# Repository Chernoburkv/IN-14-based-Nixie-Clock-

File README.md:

# IN-14-based-Nixie-Clock-
Nixie clock with date and calendar on 6 soviet nixie tubes with static indication and voltage doubler for nixies. 
Based on ds3231 and ATmega 8. Powers from 36-42VAC (for example a small transformer).
ECAD files for main & display board, Code::Blocks project, hex and fuse pic included.

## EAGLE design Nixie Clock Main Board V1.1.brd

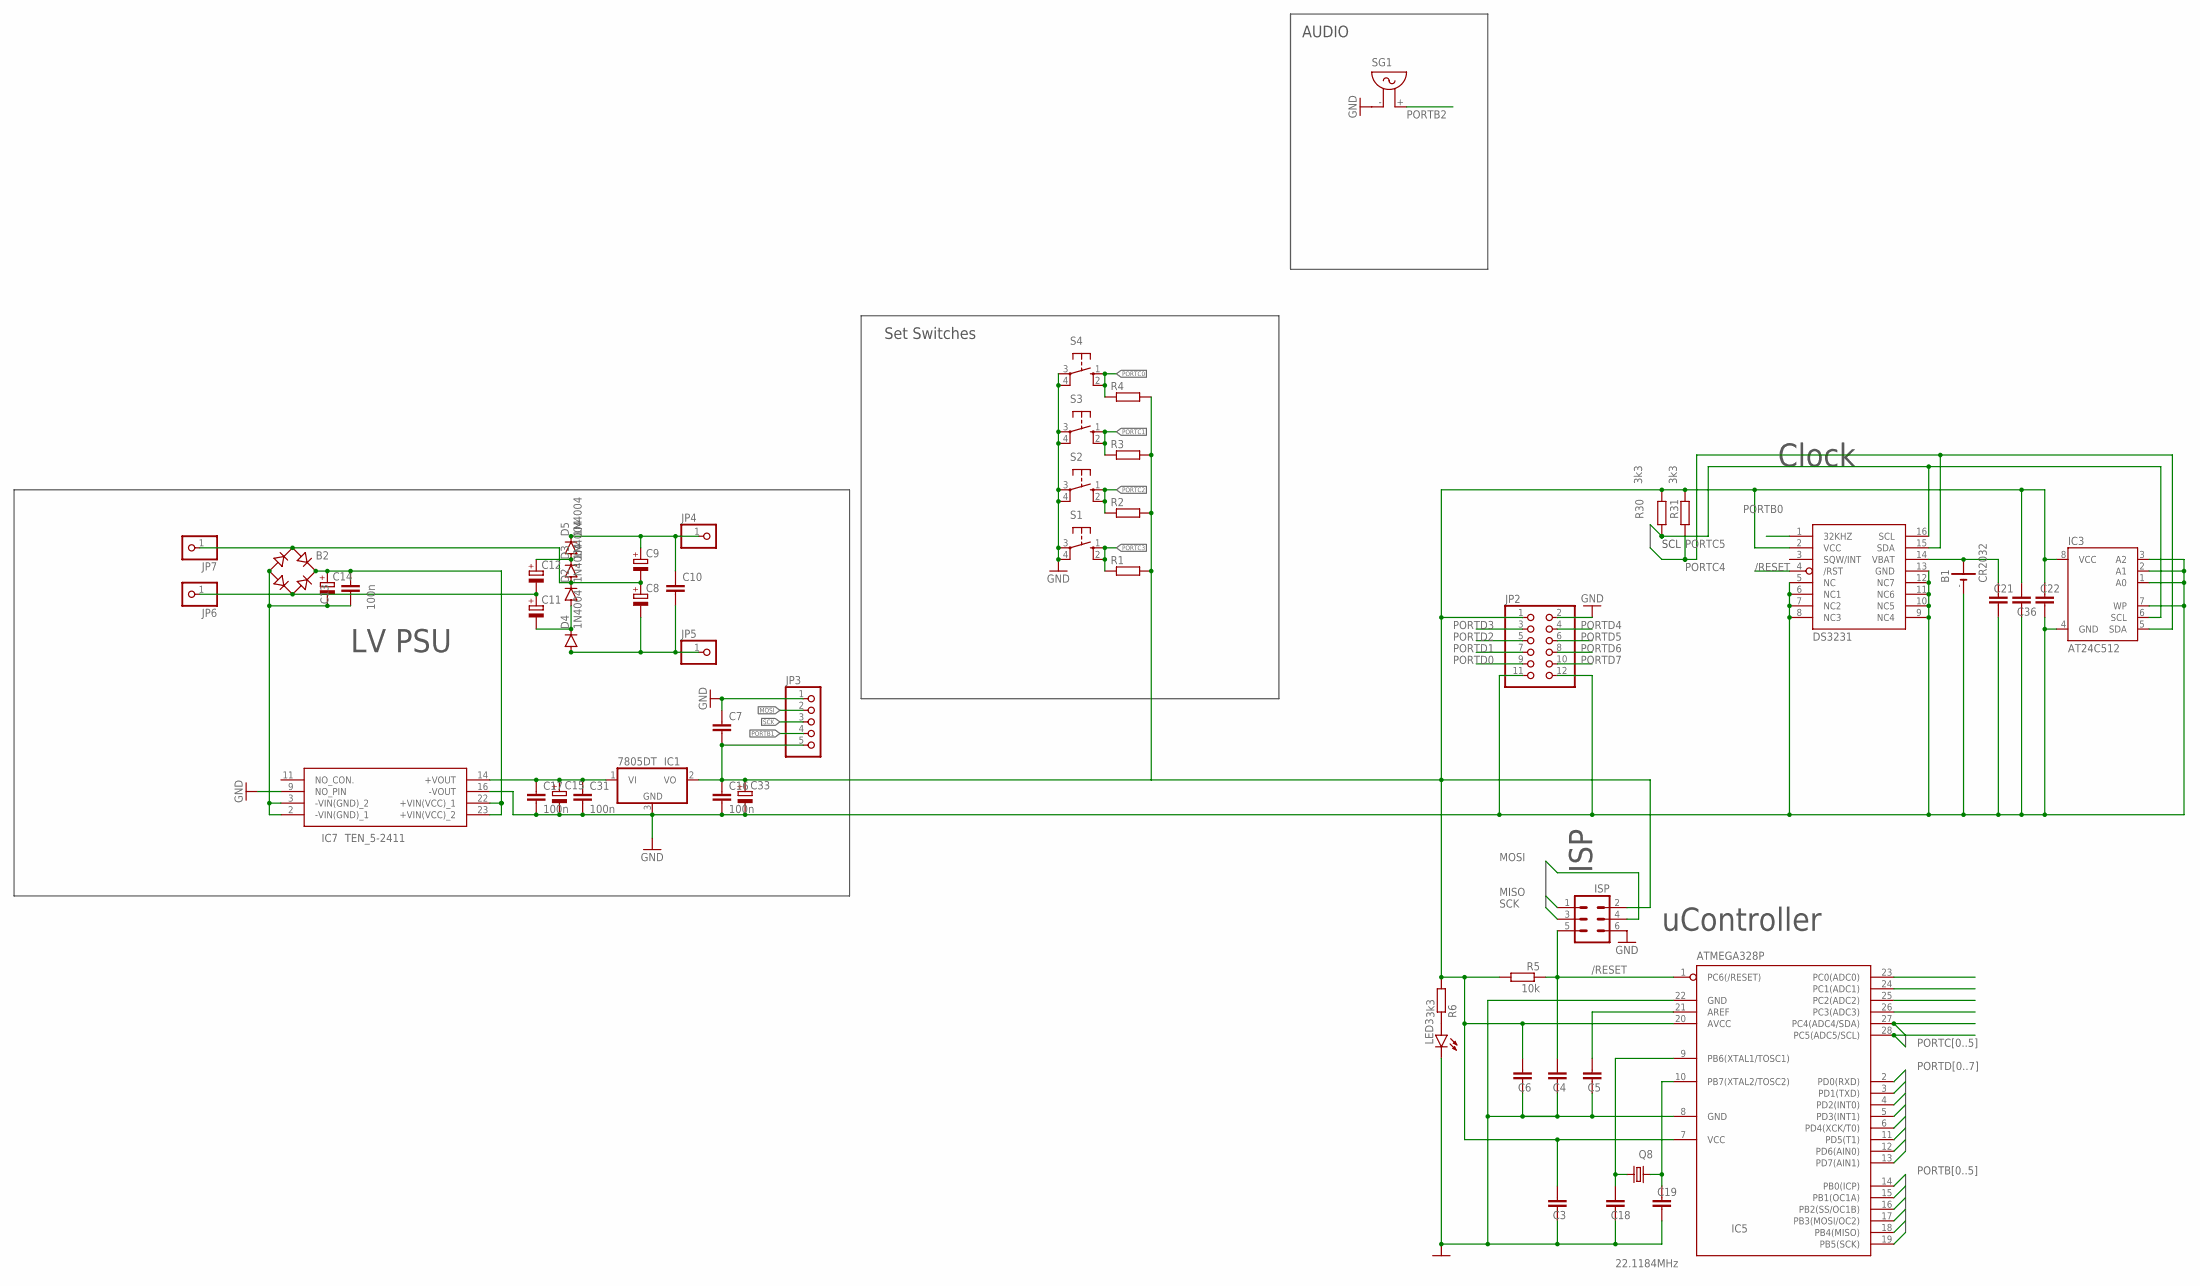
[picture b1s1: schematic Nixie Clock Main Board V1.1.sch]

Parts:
B1: CR2032
B2: B-DIL
C3, C5, C6, C21, C22, C36: C-EUC1206; C1206
C4, C7, C18, C19: C-EUC0805; C0805
C8, C9, C11, C12, C14: CPOL-EUTT5D11; TT5D11
C10: C-EU150-054X183; C150-054X183
C13: 100n; C050-025X075
C15, C33: CPOL-EUE3.5-8; E3,5-8
C16, C17, C31: 100n; C1206
D2, D3, D4, D5: 1N4004; DO41-10
IC1: 7805DT; TO252
IC3: AT24C512; DIL08
IC5: ATMEGA328P; DIL28-3
IC7: TEN_5-2411; TEN5SERIES
J: ISP; MA03-2
JP2: PINHD-2X6; 2X06
JP3: PINHD-1X5; 1X05
JP4, JP5, JP6, JP7: PINHD-1X1; 1X01
LED3: LED5MM
Q8: 22.1184MHz; HC49U-V
R1, R2, R3, R4: R-EU_R0805; R0805
R5: 10k; R0805
R6, R30, R31: 3k3; R0805
S1, S2, S3, S4: 10-XX; B3F-10XX
SG1: F/QMX
U2: DS3231; SO16W

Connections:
+5V: C3.1, C6.1, C7.2, C16.1, C22.1, C33.+, C36.1, IC1.2 (VO), IC3.8 (VCC), IC5.7 (VCC), IC5.20 (AVCC), J.2, JP2.1, JP3.5, R1.2, R2.2, R3.2, R4.2, R5.2, R6.2, R30.2, R31.2, U2.2 (VCC)
/RESET: C4.1, IC5.1 (PC6(/RESET)), J.5, R5.1, U2.4 (/RST)
GND: B1.-, C3.2, C4.2, C5.2, C6.2, C7.1, C15.-, C16.2, C17.2, C18.2, C19.2, C21.2, C22.2, C31.2, C33.-, C36.2, IC1.3 (GND), IC3.1 (A0), IC3.2 (A1), IC3.3 (A2), IC3.4 (GND), IC3.7 (WP), IC5.8 (GND), IC5.22 (GND), IC7.9 (NO_PIN), IC7.16 (-VOUT), J.6, JP2.2, JP2.11, JP2.12, JP3.1, LED3.K (C), S1.3, S1.4 (P1), S2.3, S2.4 (P1), S3.3, S3.4 (P1), S4.3, S4.4 (P1), SG1.- (1), U2.5 (NC), U2.6 (NC1), U2.7 (NC2), U2.8 (NC3), U2.9 (NC4), U2.10 (NC5), U2.11 (NC6), U2.12 (NC7), U2.13 (GND)
MISO: IC5.18 (PB4(MISO)), J.1
MOSI: IC5.17 (PB3(MOSI/OC2)), J.4, JP3.2
unnamed: C12.+, D3.C, D5.A
unnamed: B2.AC1, C8.+, C9.-, D2.C, D3.A, JP7.1
unnamed: C11.-, D2.A, D4.C
unnamed: B2.AC2, C11.+, C12.-, JP6.1
unnamed: B2.+, C13.2, C14.+, IC7.22 (+VIN(VCC)_1), IC7.23 (+VIN(VCC)_2)
unnamed: C8.-, C10.2, D4.A, JP5.1
unnamed: C9.+, C10.1, D5.C, JP4.1
unnamed: LED3.A, R6.1
unnamed: B2.-, C13.1, C14.-, IC7.2 (-VIN(GND)_1), IC7.3 (-VIN(GND)_2)
unnamed: C18.1, IC5.9 (PB6(XTAL1/TOSC1)), Q8.1
unnamed: C19.1, IC5.10 (PB7(XTAL2/TOSC2)), Q8.2
unnamed: B1.+, C21.1, U2.14 (VBAT)
unnamed: C5.1, IC5.21 (AREF)
unnamed: C15.+, C17.1, C31.1, IC1.1 (VI), IC7.14 (+VOUT)
PORTB0: IC5.14 (PB0(ICP)), U2.1 (32KHZ)
PORTB1: IC5.15 (PB1(OC1A)), JP3.4
PORTB2: IC5.16 (PB2(SS/OC1B)), SG1.+ (2)
PORTC0: IC5.23 (PC0(ADC0)), R4.1, S4.1 (S), S4.2 (S1)
PORTC1: IC5.24 (PC1(ADC1)), R3.1, S3.1 (S), S3.2 (S1)
PORTC2: IC5.25 (PC2(ADC2)), R2.1, S2.1 (S), S2.2 (S1)
PORTC3: IC5.26 (PC3(ADC3)), R1.1, S1.1 (S), S1.2 (S1)
PORTC4: IC3.5 (SDA), IC5.27 (PC4(ADC4/SDA)), R31.1, U2.15 (SDA)
PORTC5: IC3.6 (SCL), IC5.28 (PC5(ADC5/SCL)), R30.1, U2.16 (SCL)
PORTD0: IC5.2 (PD0(RXD)), JP2.9
PORTD1: IC5.3 (PD1(TXD)), JP2.7
PORTD2: IC5.4 (PD2(INT0)), JP2.5
PORTD3: IC5.5 (PD3(INT1)), JP2.3
PORTD4: IC5.6 (PD4(XCK/T0)), JP2.4
PORTD5: IC5.11 (PD5(T1)), JP2.6
PORTD6: IC5.12 (PD6(AIN0)), JP2.8
PORTD7: IC5.13 (PD7(AIN1)), JP2.10
SCK: IC5.19 (PB5(SCK)), J.3, JP3.3

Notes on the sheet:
Set Switches
AUDIO
LV PSU
Clock
uController
SCL
ISP

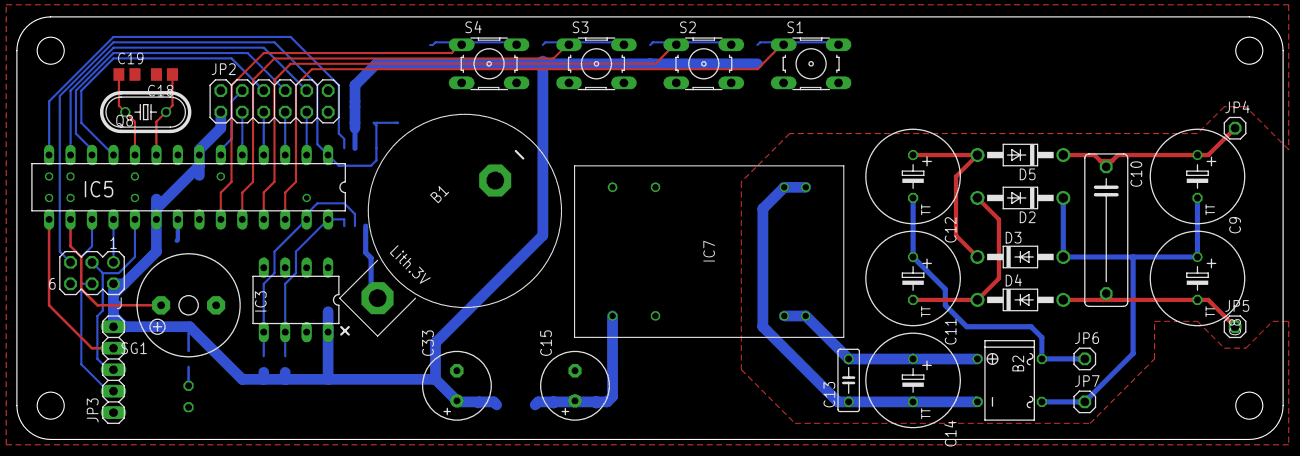
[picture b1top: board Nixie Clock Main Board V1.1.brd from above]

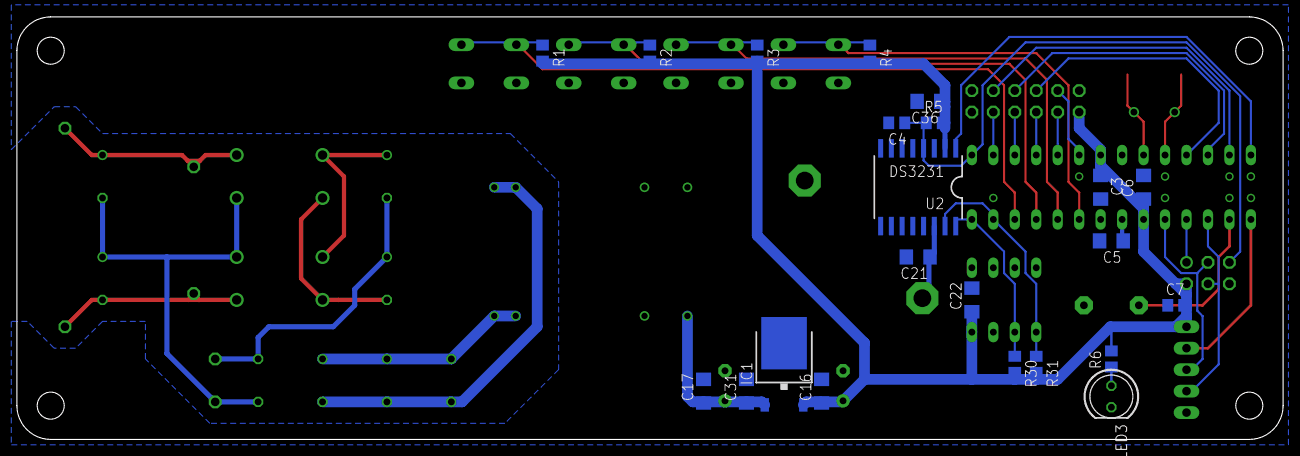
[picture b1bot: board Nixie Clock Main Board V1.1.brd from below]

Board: 2 copper layers, 149.8 x 50.0 mm, 56 parts (22 on the bottom side), 37 nets.

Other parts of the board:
U$3: 50X150

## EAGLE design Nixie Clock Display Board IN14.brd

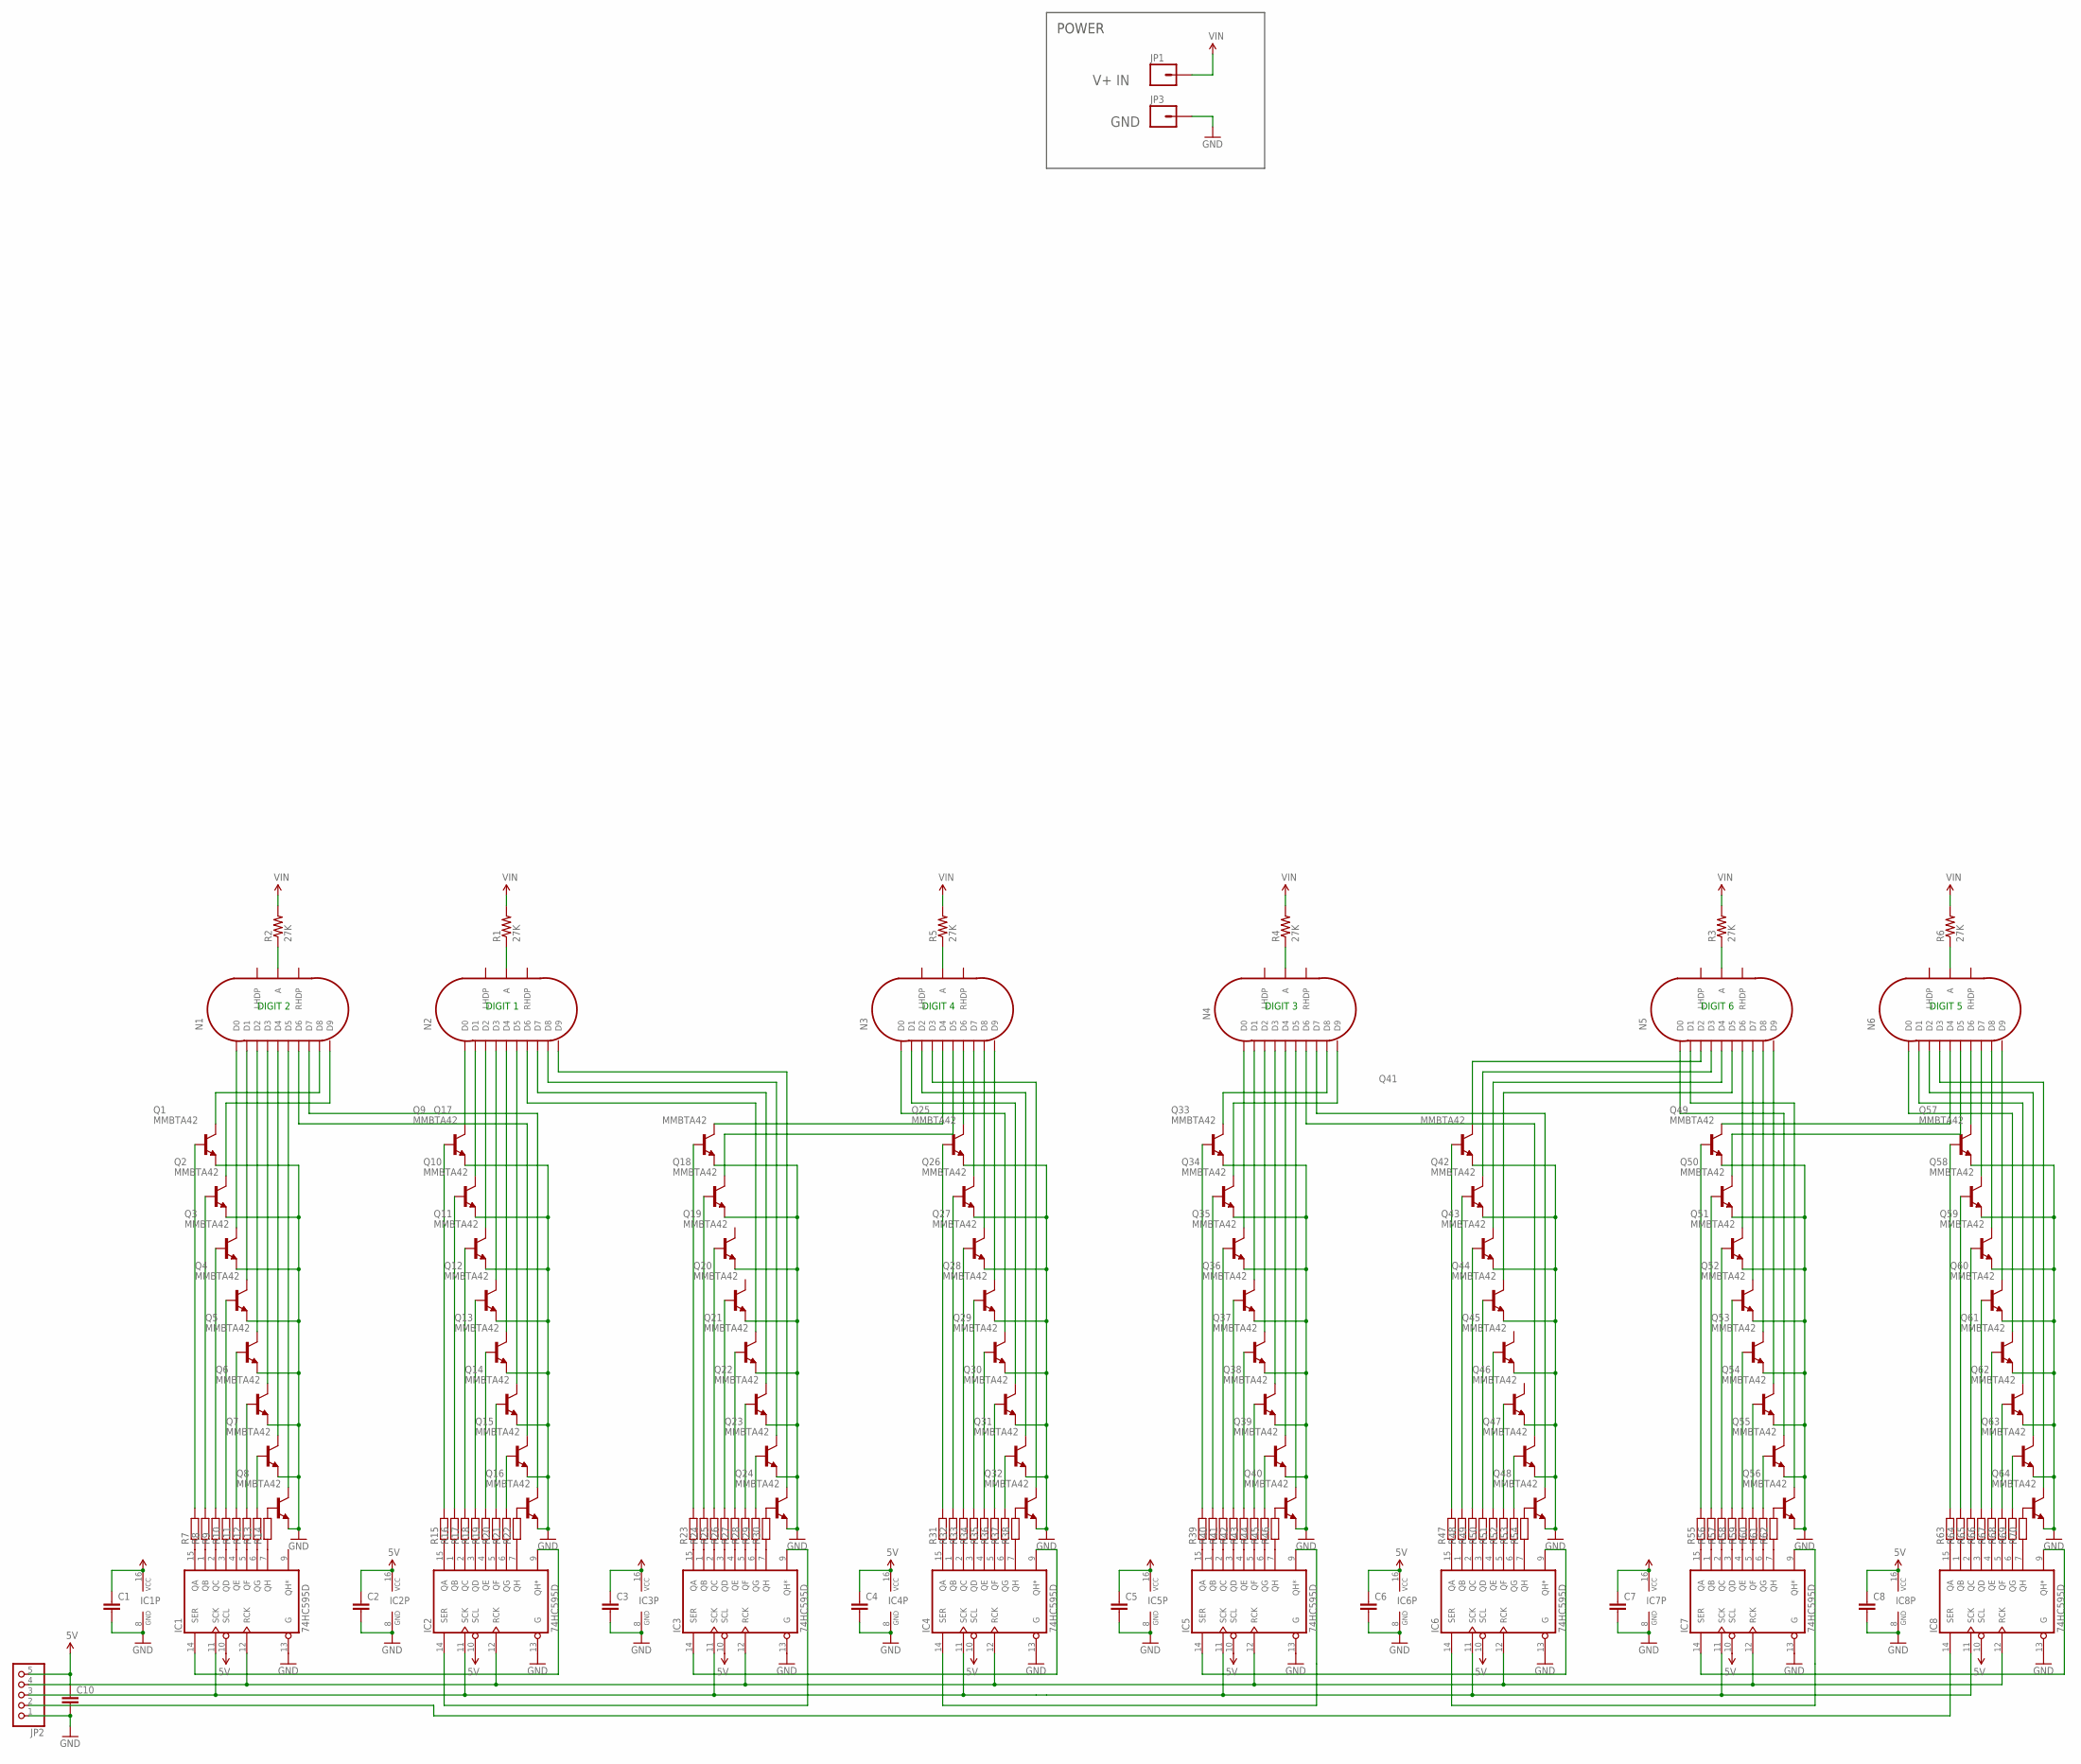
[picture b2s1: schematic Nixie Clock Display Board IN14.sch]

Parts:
C1, C2, C3, C4, C5, C6, C7, C8, C10: C-EUC0805; C0805
IC1, IC2, IC3, IC4, IC5, IC6, IC7, IC8: 74HC595D; SO16
JP1, JP3: M01PTH; 1X01
JP2: PINHD-1X5; 1X05
N1, N2, N3, N4, N5, N6: IN-14
Q1, Q2, Q3, Q4, Q5, Q6, Q7, Q8, Q9, Q10, Q11, Q12, Q13, Q14, Q15, Q16, Q17, Q18, Q19, Q20, Q21, Q22, Q23, Q24, Q25, Q26, Q27, Q28, Q29, Q30, Q31, Q32, Q33, Q34, Q35, Q36, Q37, Q38, Q39, Q40, Q41, Q42, Q43, Q44, Q45, Q46, Q47, Q48, Q49, Q50, Q51, Q52, Q53, Q54, Q55, Q56, Q57, Q58, Q59, Q60, Q61, Q62, Q63, Q64: MMBTA42; SOT23
R1, R2, R3, R4, R5, R6: 27K; AXIAL-0.5
R7, R8, R9, R10, R11, R12, R13, R14, R15, R16, R17, R18, R19, R20, R21, R22, R23, R24, R25, R26, R27, R28, R29, R30, R31, R32, R33, R34, R35, R36, R37, R38, R39, R40, R41, R42, R43, R44, R45, R46, R47, R48, R49, R50, R51, R52, R53, R54, R55, R56, R57, R58, R59, R60, R61, R62, R63, R64, R65, R66, R67, R68, R69, R70: R-EU_R0805; R0805

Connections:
5V: C1.1, C2.1, C3.1, C4.1, C5.1, C6.1, C7.1, C8.1, C10.1, IC1.10 (SCL), IC1.16 (VCC), IC2.10 (SCL), IC2.16 (VCC), IC3.10 (SCL), IC3.16 (VCC), IC4.10 (SCL), IC4.16 (VCC), IC5.10 (SCL), IC5.16 (VCC), IC6.10 (SCL), IC6.16 (VCC), IC7.10 (SCL), IC7.16 (VCC), IC8.10 (SCL), IC8.16 (VCC), JP2.5
GND: C1.2, C2.2, C3.2, C4.2, C5.2, C6.2, C7.2, C8.2, C10.2, IC1.8 (GND), IC1.13 (G), IC2.8 (GND), IC2.13 (G), IC3.8 (GND), IC3.13 (G), IC4.8 (GND), IC4.13 (G), IC5.8 (GND), IC5.13 (G), IC6.8 (GND), IC6.13 (G), IC7.8 (GND), IC7.13 (G), IC8.8 (GND), IC8.13 (G), JP2.1, JP3.1, Q1.2 (E), Q2.2 (E), Q3.2 (E), Q4.2 (E), Q5.2 (E), Q6.2 (E), Q7.2 (E), Q8.2 (E), Q9.2 (E), Q10.2 (E), Q11.2 (E), Q12.2 (E), Q13.2 (E), Q14.2 (E), Q15.2 (E), Q16.2 (E), Q17.2 (E), Q18.2 (E), Q19.2 (E), Q20.2 (E), Q21.2 (E), Q22.2 (E), Q23.2 (E), Q24.2 (E), Q25.2 (E), Q26.2 (E), Q27.2 (E), Q28.2 (E), Q29.2 (E), Q30.2 (E), Q31.2 (E), Q32.2 (E), Q33.2 (E), Q34.2 (E), Q35.2 (E), Q36.2 (E), Q37.2 (E), Q38.2 (E), Q39.2 (E), Q40.2 (E), Q41.2 (E), Q42.2 (E), Q43.2 (E), Q44.2 (E), Q45.2 (E), Q46.2 (E), Q47.2 (E), Q48.2 (E), Q49.2 (E), Q50.2 (E), Q51.2 (E), Q52.2 (E), Q53.2 (E), Q54.2 (E), Q55.2 (E), Q56.2 (E), Q57.2 (E), Q58.2 (E), Q59.2 (E), Q60.2 (E), Q61.2 (E), Q62.2 (E), Q63.2 (E), Q64.2 (E)
IN1: IC8.14 (SER), JP2.2
IN2: IC1.12 (RCK), IC2.12 (RCK), IC3.12 (RCK), IC4.12 (RCK), IC5.12 (RCK), IC6.12 (RCK), IC7.12 (RCK), IC8.12 (RCK), JP2.4
IN5: IC1.11 (SCK), IC2.11 (SCK), IC3.11 (SCK), IC4.11 (SCK), IC5.11 (SCK), IC6.11 (SCK), IC7.11 (SCK), IC8.11 (SCK), JP2.3
IN7: IC2.14 (SER), IC3.9 (QH*)
IN8: IC4.14 (SER), IC5.9 (QH*)
IN12: IC5.14 (SER), IC6.9 (QH*)
IN13: IC6.14 (SER), IC7.9 (QH*)
unnamed: Q1.1 (B), R7.2
unnamed: IC1.15 (QA), R7.1
unnamed: IC1.1 (QB), R8.1
unnamed: IC1.2 (QC), R9.1
unnamed: IC1.3 (QD), R10.1
unnamed: IC1.4 (QE), R11.1
unnamed: IC1.5 (QF), R12.1
unnamed: IC1.6 (QG), R13.1
unnamed: IC1.7 (QH), R14.1
unnamed: Q8.1 (B), R14.2
unnamed: Q7.1 (B), R13.2
unnamed: Q6.1 (B), R12.2
unnamed: Q5.1 (B), R11.2
unnamed: Q4.1 (B), R10.2
unnamed: Q3.1 (B), R9.2
unnamed: Q2.1 (B), R8.2
unnamed: Q9.1 (B), R15.2
unnamed: Q16.1 (B), R22.2
unnamed: Q15.1 (B), R21.2
unnamed: Q14.1 (B), R20.2
unnamed: Q13.1 (B), R19.2
unnamed: Q12.1 (B), R18.2
unnamed: Q11.1 (B), R17.2
unnamed: Q10.1 (B), R16.2
unnamed: N6.D0, Q61.3 (C)
unnamed: IC1.14 (SER), IC2.9 (QH*)
unnamed: N5.A, R3.P$1 (1)
unnamed: IC2.15 (QA), R15.1
unnamed: IC2.1 (QB), R16.1
unnamed: IC2.2 (QC), R17.1
unnamed: IC2.3 (QD), R18.1
unnamed: IC2.4 (QE), R19.1
unnamed: IC2.5 (QF), R20.1
unnamed: IC2.6 (QG), R21.1
unnamed: IC2.7 (QH), R22.1
unnamed: Q17.1 (B), R23.2
unnamed: Q24.1 (B), R30.2
unnamed: N6.A, R6.P$1 (1)
unnamed: Q23.1 (B), R29.2
unnamed: Q22.1 (B), R28.2
unnamed: Q21.1 (B), R27.2
unnamed: Q20.1 (B), R26.2
unnamed: Q19.1 (B), R25.2
unnamed: Q18.1 (B), R24.2
unnamed: IC3.15 (QA), R23.1
unnamed: IC3.1 (QB), R24.1
unnamed: IC3.2 (QC), R25.1
unnamed: IC3.3 (QD), R26.1
unnamed: IC3.4 (QE), R27.1
unnamed: IC3.5 (QF), R28.1
unnamed: IC3.6 (QG), R29.1
unnamed: IC3.7 (QH), R30.1
unnamed: N4.A, R4.P$1 (1)
unnamed: N3.A, R5.P$1 (1)
unnamed: IC3.14 (SER), IC4.9 (QH*)
unnamed: N6.D1, Q62.3 (C)
unnamed: IC7.14 (SER), IC8.9 (QH*)
unnamed: N6.D2, Q63.3 (C)
unnamed: N6.D3, Q64.3 (C)
unnamed: Q25.1 (B), R31.2
unnamed: Q32.1 (B), R38.2
unnamed: Q31.1 (B), R37.2
unnamed: Q30.1 (B), R36.2
unnamed: Q29.1 (B), R35.2
unnamed: Q28.1 (B), R34.2
unnamed: Q27.1 (B), R33.2
unnamed: Q26.1 (B), R32.2
unnamed: IC4.15 (QA), R31.1
unnamed: IC4.1 (QB), R32.1
unnamed: IC4.2 (QC), R33.1
unnamed: IC4.3 (QD), R34.1
unnamed: IC4.4 (QE), R35.1
unnamed: IC4.5 (QF), R36.1
unnamed: IC4.6 (QG), R37.1
unnamed: IC4.7 (QH), R38.1
unnamed: Q33.1 (B), R39.2
unnamed: Q40.1 (B), R46.2
unnamed: Q39.1 (B), R45.2
unnamed: Q38.1 (B), R44.2
unnamed: N2.A, R1.P$1 (1)
unnamed: N1.A, R2.P$1 (1)
unnamed: N6.D4, Q49.3 (C)
unnamed: N6.D5, Q50.3 (C)
unnamed: N6.D6, Q57.3 (C)
unnamed: N6.D7, Q58.3 (C)
unnamed: N6.D8, Q59.3 (C)
unnamed: N6.D9, Q60.3 (C)
unnamed: Q37.1 (B), R43.2
unnamed: Q36.1 (B), R42.2
unnamed: Q35.1 (B), R41.2
unnamed: Q34.1 (B), R40.2
unnamed: IC5.15 (QA), R39.1
unnamed: IC5.1 (QB), R40.1
unnamed: IC5.2 (QC), R41.1
unnamed: IC5.3 (QD), R42.1
unnamed: N3.D0, Q29.3 (C)
unnamed: N3.D1, Q30.3 (C)
unnamed: N3.D2, Q31.3 (C)
unnamed: N3.D3, Q32.3 (C)
unnamed: N3.D4, Q17.3 (C)
unnamed: N5.D0, Q55.3 (C)
unnamed: N3.D5, Q18.3 (C)
unnamed: N3.D6, Q25.3 (C)
unnamed: N3.D7, Q26.3 (C)
unnamed: N3.D8, Q27.3 (C)
unnamed: N3.D9, Q28.3 (C)
unnamed: IC5.4 (QE), R43.1
unnamed: IC5.5 (QF), R44.1
unnamed: IC5.6 (QG), R45.1
unnamed: IC5.7 (QH), R46.1
unnamed: Q41.1 (B), R47.2
unnamed: Q48.1 (B), R54.2
unnamed: Q47.1 (B), R53.2
unnamed: Q46.1 (B), R52.2
unnamed: N2.D0, Q9.3 (C)
unnamed: N2.D1, Q10.3 (C)
unnamed: N2.D2, Q11.3 (C)
unnamed: N2.D3, Q12.3 (C)
unnamed: N2.D4, Q13.3 (C)
unnamed: N2.D5, Q14.3 (C)
unnamed: N2.D6, Q21.3 (C)
unnamed: N2.D7, Q22.3 (C)
unnamed: N2.D8, Q23.3 (C)
unnamed: N2.D9, Q24.3 (C)
unnamed: N1.D0, Q3.3 (C)
unnamed: N1.D1, Q4.3 (C)
unnamed: N1.D2, Q5.3 (C)
unnamed: N1.D3, Q6.3 (C)
unnamed: N1.D4, Q7.3 (C)
unnamed: N1.D5, Q8.3 (C)
unnamed: N1.D6, Q15.3 (C)
unnamed: N1.D7, Q16.3 (C)
unnamed: N1.D8, Q1.3 (C)
unnamed: N1.D9, Q2.3 (C)
unnamed: Q45.1 (B), R51.2
unnamed: Q44.1 (B), R50.2
unnamed: Q43.1 (B), R49.2
unnamed: Q42.1 (B), R48.2
unnamed: IC6.15 (QA), R47.1
unnamed: IC6.1 (QB), R48.1
unnamed: IC6.2 (QC), R49.1
unnamed: IC6.3 (QD), R50.1
unnamed: IC6.4 (QE), R51.1
unnamed: IC6.5 (QF), R52.1
unnamed: IC6.6 (QG), R53.1
unnamed: IC6.7 (QH), R54.1
unnamed: Q49.1 (B), R55.2
unnamed: Q56.1 (B), R62.2
unnamed: Q55.1 (B), R61.2
unnamed: Q54.1 (B), R60.2
unnamed: Q53.1 (B), R59.2
unnamed: Q52.1 (B), R58.2
unnamed: Q51.1 (B), R57.2
unnamed: Q50.1 (B), R56.2
unnamed: IC7.15 (QA), R55.1
unnamed: IC7.1 (QB), R56.1
unnamed: IC7.2 (QC), R57.1
unnamed: IC7.3 (QD), R58.1
unnamed: IC7.4 (QE), R59.1
unnamed: IC7.5 (QF), R60.1
unnamed: IC7.6 (QG), R61.1
unnamed: IC7.7 (QH), R62.1
unnamed: Q57.1 (B), R63.2
unnamed: Q64.1 (B), R70.2
unnamed: Q63.1 (B), R69.2
unnamed: Q62.1 (B), R68.2
unnamed: Q61.1 (B), R67.2
unnamed: Q60.1 (B), R66.2
unnamed: Q59.1 (B), R65.2
unnamed: Q58.1 (B), R64.2
unnamed: IC8.15 (QA), R63.1
unnamed: IC8.1 (QB), R64.1
unnamed: IC8.2 (QC), R65.1
unnamed: IC8.3 (QD), R66.1
unnamed: IC8.4 (QE), R67.1
unnamed: IC8.5 (QF), R68.1
unnamed: IC8.6 (QG), R69.1
unnamed: IC8.7 (QH), R70.1
unnamed: N5.D1, Q56.3 (C)
unnamed: N5.D2, Q41.3 (C)
unnamed: N5.D3, Q42.3 (C)
unnamed: N5.D4, Q43.3 (C)
unnamed: N5.D5, Q44.3 (C)
unnamed: N5.D6, Q51.3 (C)
unnamed: N5.D7, Q52.3 (C)
unnamed: N5.D8, Q53.3 (C)
unnamed: N5.D9, Q54.3 (C)
unnamed: N4.D0, Q35.3 (C)
unnamed: N4.D1, Q36.3 (C)
unnamed: N4.D2, Q37.3 (C)
unnamed: N4.D3, Q38.3 (C)
unnamed: N4.D4, Q39.3 (C)
unnamed: N4.D5, Q40.3 (C)
unnamed: N4.D6, Q47.3 (C)
unnamed: N4.D7, Q48.3 (C)
unnamed: N4.D8, Q33.3 (C)
unnamed: N4.D9, Q34.3 (C)
VIN: JP1.1, R1.P$2 (2), R2.P$2 (2), R3.P$2 (2), R4.P$2 (2), R5.P$2 (2), R6.P$2 (2)

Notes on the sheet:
V+ IN
DIGIT 6
DIGIT 5
POWER
GND
DIGIT 4
DIGIT 3
DIGIT 2
DIGIT 1

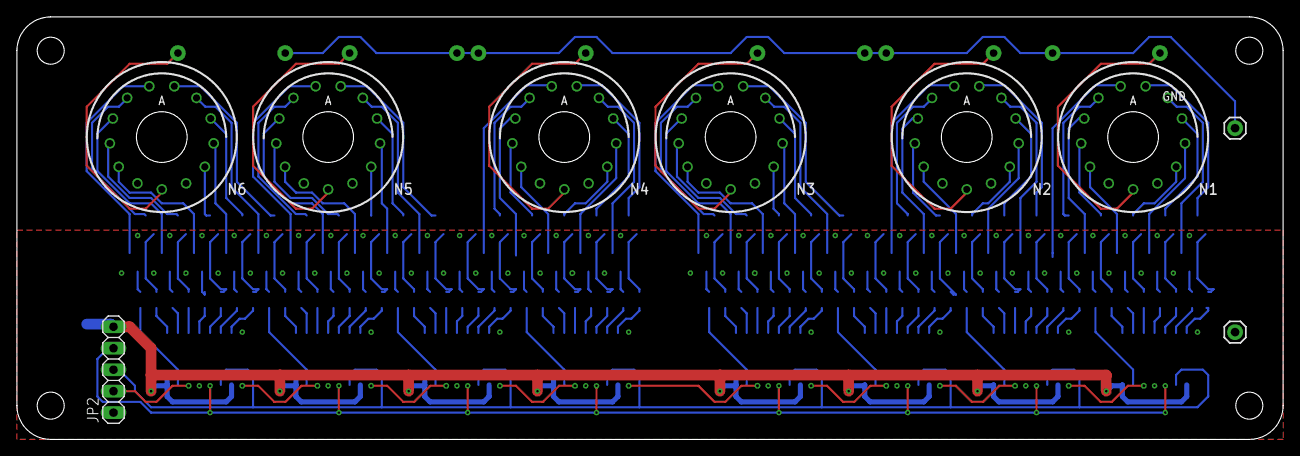
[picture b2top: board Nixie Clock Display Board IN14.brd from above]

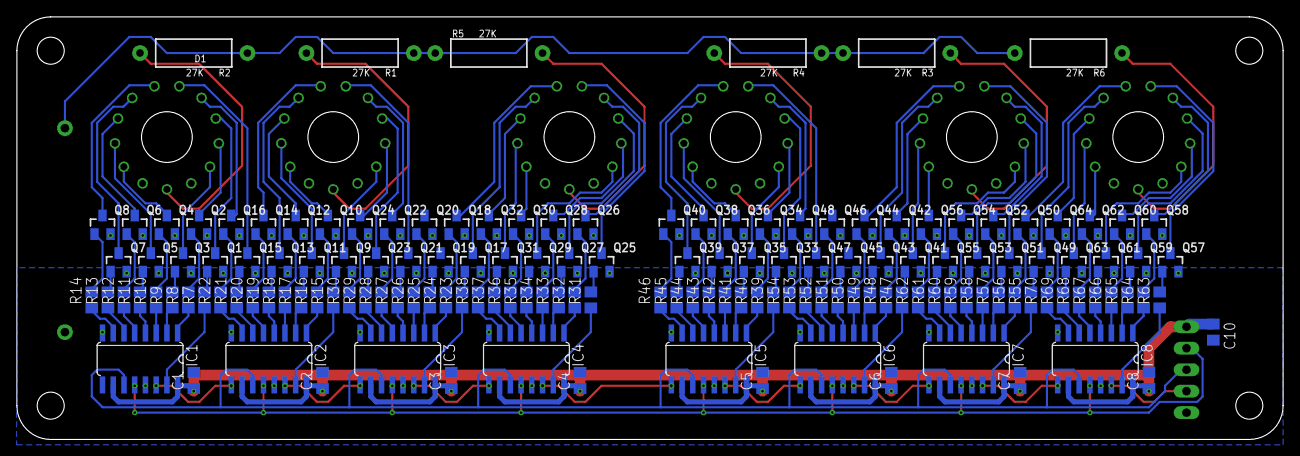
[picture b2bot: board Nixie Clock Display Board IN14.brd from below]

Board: 2 copper layers, 149.8 x 50.0 mm, 161 parts (151 on the bottom side), 207 nets.

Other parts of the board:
U$1: 50X150

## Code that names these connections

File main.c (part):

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
#define SHIFT_REGISTER DDRB
#define SHIFT_PORT PORTB
#define LATCH (1<< PORTB1)     // LATCH
#define SS (1<< PORTB2)       // SS (NC)
#define DATA (1<< PORTB3)    //MOSI (SI)
#define CLOCK (1<< PORTB5)  //SCK (SCK)

#define BUTTON_REGISTER DDRC
#define BUTTON_PIN PINC
#define B0 (1 << PC0)    //0
#define B1 (1 << PC1)    //1
#define B2 (1 << PC2)    //2
#define B3 (1 << PC3)    //3

uint8_t dispstat=0;
uint8_t dispon=0;
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

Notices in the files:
parts and their libraries:
SparkFun-Resistors: Licensing: Creative Commons ShareAlike 4.0 International - https://creativecommons.org/licenses/by-sa/4.0
